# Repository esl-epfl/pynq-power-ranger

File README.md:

<div align="center">
    
</div>

## 🚀 Overview

The **Pynq Power Ranger** is a shield designed for the Xilinx Pynq-Z2 SoC board, enabling real-time power consumption measurement of the entire board. The repository contains the necessary PCB files to manufacture the power measurement shield together with the IP configuration to control the current measurement from Linux running on the processing system. The shield measures the voltage drop across a shunt resistor placed in series with the Pynq-Z2 power supply line using the ADC of the FPGA chip.

## 📦 Repository Contents
- **[Software Support](SW_Examples/README.md)**: The IP and driver to measure the current from the processing system and one application example that uses the Pynq Power Ranger to compute the energy consumption.
- **[Schematics & PCB](PCB_Design/README.md)**: A description of the board design and the KiCad files for board design, production, and hand/PnP assembly.

## ⚙️ Features

### ⚡ Selectable Input Power Supply
The switch **SW1 (PWR)** selects the power source of the Pynq-Z2 board:
- **Left**: The USB Micro-B Connector (5.0 V)
- **Right**: The DC Jack (7.0 V - 15.0 V, post-regulated to 5.0 V)

> [!WARNING]
> This switch replaces the jumper of the board. If the correct source is not selected, the board will not power up.

### 🎯 Selectable ADC Input Range and Precision
Use **SW2 (ANA)** to toggle between the inputs:
- **Left**: Specialized pin of the XADC of the chip (VP) -> Used by the Software Support examples
- **Right**: An alternative Arduino A0 pin. Internally connected to a 3:1 resistor voltage divider that outputs (1.0 V when the input voltage is 3.3 V). This allows for a wider input range at the cost of resolution.

<div align="center">

| Input Pin | Saturation Point | Resolution |
|-----------|------------------|------------|
| VP        | 1.25 A           | 0.3 mA     |
| A0        | 3.75 A           | 1.0 mA     |

</div>

> [!WARNING]
> The onboard ADC of the Pynq-Z2 board has a reference voltage of 1.0 V, which defines the saturation point of the measurement. If the current exceeds this value, the measurement will saturate and will not be accurate.

### 🧵 Thread-based Measurements
The software examples provided in this repository use a thread-based approach to continuously monitor the current consumption to accurately estimate energy consumption. This allows for real-time data acquisition and processing without blocking the main application.

## Contact
For additional information, please contact the authors:
- **Alex López**: [alejandro.lopezrodriguez@epfl.ch](mailto:alejandro.lopezrodriguez@epfl.ch)
- **Rubén Rodríguez**: [ruben.rodriguezalvarez@epfl.ch](mailto:ruben.rodriguezalvarez@epfl.ch)
- **Miguel Peón**: [miguel.peon@epfl.ch](mailto:miguel.peon@epfl.ch)

Developed at the **[Embedded Systems Laboratory (ESL), EPFL](https://www.epfl.ch/labs/esl/research/)**.

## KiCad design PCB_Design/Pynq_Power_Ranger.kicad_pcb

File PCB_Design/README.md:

# PCB Design for Pynq Power Ranger

<div align="center">
    
</div>

## 🚀 Description

This folder contains all the necessary files to manufacture the Pynq Power Ranger board. The design has been created using [KiCad EDA](https://kicad.org/).

## 📁 Repository Contents

- **KiCad Project Files**: The complete KiCad project files for the Pynq Power Ranger board.
- **Gerber Files**: The Gerber files required for PCB manufacturing.
- **BOM (Bill of Materials)**: A comprehensive list of all components used in the design.
- **Schematic Diagrams**: The schematic diagrams of the Pynq Power Ranger board.
- **PCB Layout**: The PCB layout files showing the physical arrangement of components and traces.

## 🔧 Design Overview

The board implements the following functionalities:
- A **shunt resistor** for current sensing.
- A **precision transimpedance amplifier** (INA214) to amplify the voltage drop across the shunt resistor.
- An ADC input connected to the FPGA's **XADC module** for voltage measurement.
- A **selectable input range** using a switch to choose between two different ADC input pins (VP and Arduino A0).
- A **power supply selection** switch to choose between USB and DC jack input for the Pynq-Z2 board.
- An **SMA connector** for direct voltage measurement with an oscilloscope.

### Input Range and Resolution
- **Arduino-compatible pins**: Internally connected to a resistor voltage divider that outputs **1.0 V when the input voltage is 3.3 V**. This allows for a wider input range at the cost of resolution.
- **VP pin**: Directly connected to the ADC input, providing better resolution but a lower range.

The amplifier has a **gain of 100 V/V**, and the **shunt resistor is 8 mΩ**. Thus, the INA214 output voltage is:

$$ V_{INA} = (I_{LOAD} \times 0.008 \ \Omega) \times 100 \text{ V/V} $$

- **For the VP pin ($V_{VP} = V_{INA}$)**, saturation occurs at $I_{LOAD}$ = 1.25 A ($V_{INA} = V_{ADC \ REF}$ = 1.0 V).

>[!CAUTION]
> If higher currents are required (e.g., for powering external PMODs), switch to **A0 mode**.

The output of the transimpedance amplifier is also routed to the SMA connector on the right side of the board, enabling a direct connection to an oscilloscope with high input impedance.

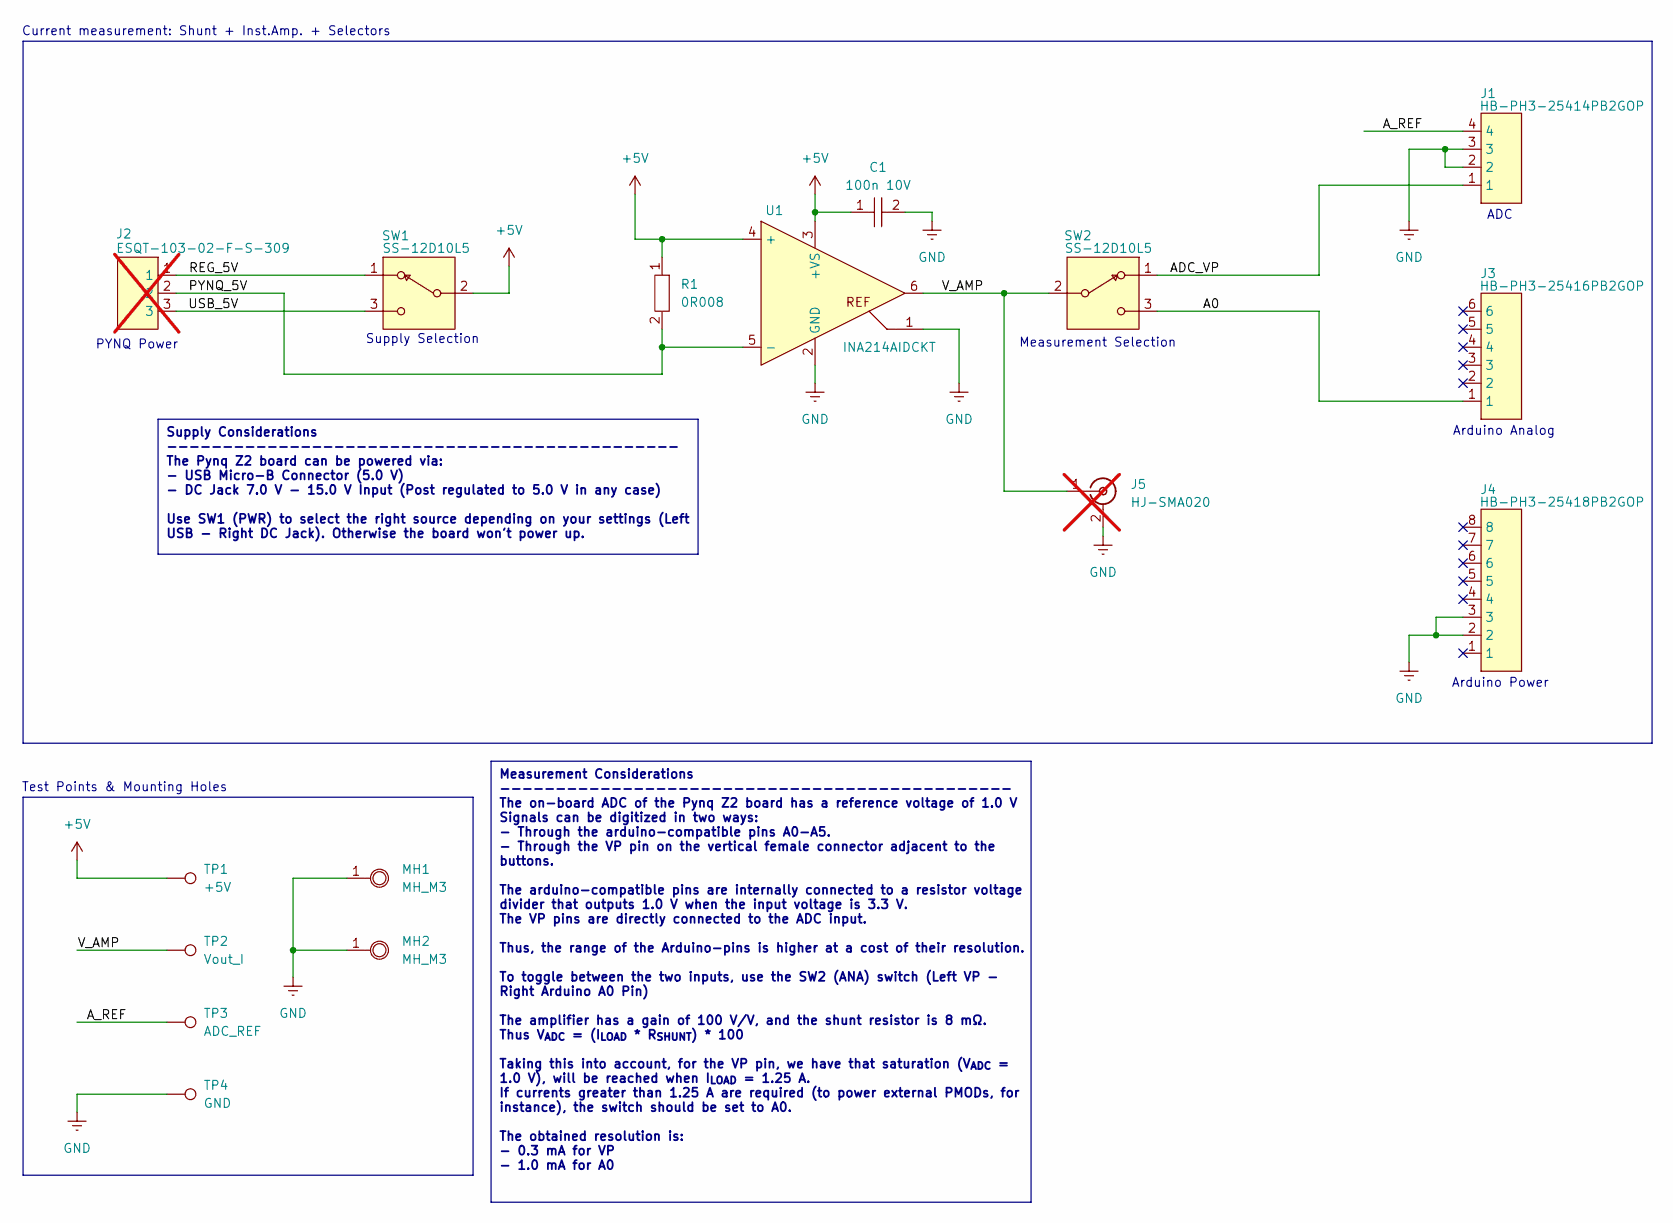
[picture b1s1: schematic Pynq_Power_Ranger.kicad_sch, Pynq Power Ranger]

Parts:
C1: 100n 10V; C0805; MPN C0805C104M3RACTU; LCSC C2168659
J1: HB-PH3-25414PB2GOP; 4-Row_Header_2.54mm; MPN HB-PH3-25414PB2GOP; LCSC C6332197
J2: ESQT-103-02-F-S-309; MPN ESQT-103-02-F-S-309; not fitted
J3: HB-PH3-25416PB2GOP; 6-Row_Header_2.54mm; MPN HB-PH3-25416PB2GOP; LCSC C6332199
J4: HB-PH3-25418PB2GOP; 8-Row_Header_2.54mm; MPN HB-PH3-25418PB2GOP; LCSC C6332201
J5: HJ-SMA020; MPN HJ-SMA020; LCSC C1509232; not fitted
MH1, MH2: MH_M3
R1: 0R008; R0805; MPN PA0805FRE470R008L; LCSC C728269
SW1, SW2: SS-12D10L5; MPN SS-12D10L5; LCSC C319012
TP1: +5V; TestPoint_Pad_D2.0mm
TP2: Vout_I; TestPoint_Pad_D2.0mm
TP3: ADC_REF; TestPoint_Pad_D2.0mm
TP4: GND; TestPoint_Pad_D2.0mm
U1: INA214AIDCKT; SC70-6; MPN INA214AIDCKT; LCSC C105240

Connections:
+5V: C1.1, R1.1, SW1.2, TP1.1, U1.3 (+VS), U1.4 (+)
/A0: J3.1, SW2.3
/ADC_VP: J1.1, SW2.1
/A_REF: J1.4, TP3.1
/PYNQ_5V: J2.2, R1.2, U1.5 (-)
/REG_5V: J2.1, SW1.1
/USB_5V: J2.3, SW1.3
/V_AMP: J5.1, SW2.2, TP2.1, U1.6
GND: C1.2, J1.2, J1.3, J4.2, J4.3, J5.2, MH1.1, MH2.1, TP4.1, U1.1, U1.2 (GND)

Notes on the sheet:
Supply Considerations ---------------------------------------------- The Pynq Z2 board can be powered via: - USB Micro-B Connector (5.0 V) - DC Jack 7.0 V - 15.0 V Input (Post regulated to 5.0 V in any case) Use SW1 (PWR) to select the right source depending on your settings (Left USB - Right DC Ja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
Measurement Considerations ---------------------------------------------- The on-board ADC of the Pynq Z2 board has a reference voltage of 1.0 V Signals can be digitized in two ways: - Through the arduino-compatible pins A0-A5. - Through the VP pin on the vertical female connector adjacent to the b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
Arduino Power
Current measurement: Shunt + Inst.Amp. + Selectors
ADC
Arduino Analog
Measurement Selection
Supply Selection
Test Points & Mounting Holes
PYNQ Power

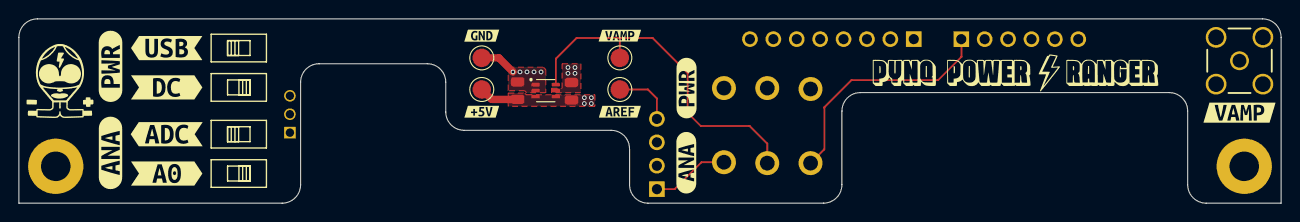
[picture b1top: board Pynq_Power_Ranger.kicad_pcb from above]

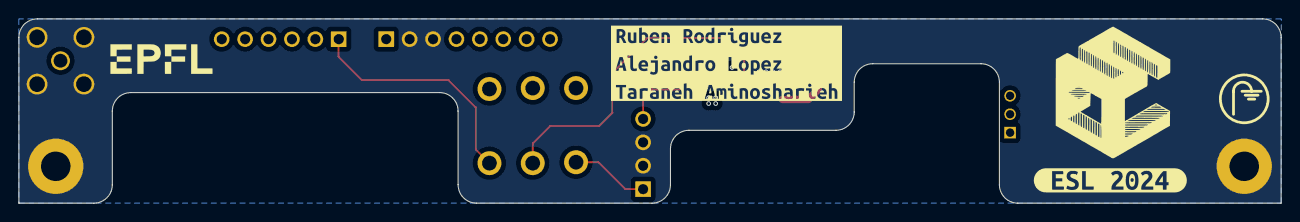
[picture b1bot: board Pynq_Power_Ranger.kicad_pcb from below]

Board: 4 copper layers, 137.0 x 20.0 mm, 31 parts (5 on the bottom side), 9 nets.

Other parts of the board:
kibuzzard-68C055AF: G***; kibuzzard-68C055AF
kibuzzard-68C055B7: G***; kibuzzard-68C055B7
kibuzzard-6703B37F: G***; kibuzzard-6703B37F
kibuzzard-6703B435: G***; kibuzzard-6703B435
kibuzzard-67001D02: G***; kibuzzard-67001D02
kibuzzard-67001D4B: G***; kibuzzard-67001D4B
kibuzzard-67001D32: G***; kibuzzard-67001D32
kibuzzard-67001D54: G***; kibuzzard-67001D54
kibuzzard-67001FBD: G***; kibuzzard-67001FBD
kibuzzard-67001FE8: G***; kibuzzard-67001FE8
kibuzzard-67080F4D: G***; kibuzzard-67080F4D
kibuzzard-670020E4: G***; kibuzzard-670020E4
kibuzzard-6700203E: G***; kibuzzard-6700203E
kibuzzard-67002037: G***; kibuzzard-67002037
kibuzzard-67002108: G***; kibuzzard-67002108

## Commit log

2025-09-08 Adding initial examples for use of the Pynq Power Ranger.
2025-09-15 Added PCB files, gitignore, README.
2025-09-15 updated gitignore
2025-09-16 Full documentation
2025-09-16 Fix image reference
2025-09-16 Fix typo in the sample frequency
2025-09-16 fixed typo in readme
2025-09-16 fixed markdown note/warning boxes syntax
2025-09-16 Fixed markdown syntax for caution box
2025-09-16 Improve warning formatting in README
2025-09-16 Modify image alt text and center input table
    Updated image alt text and formatted input table.
2025-09-16 Add license
2025-09-16 Update ESL link in README
